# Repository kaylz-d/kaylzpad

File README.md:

# kaylzpad
This is an angel-shaped keypad that I made for Highway to Undercity (Hackpad)!

## Schematic

## PCB

## Model

## BOM
- 5x Cherry MX Switches
- 5x DSA keycaps
- 4x M3x5x4 heatset inserts
- 4x M3x16mm screws
- 3x SK6812 MINI-E LEDs
- 1x XIAO RP2040
- 1x 3D printed case (2 components)

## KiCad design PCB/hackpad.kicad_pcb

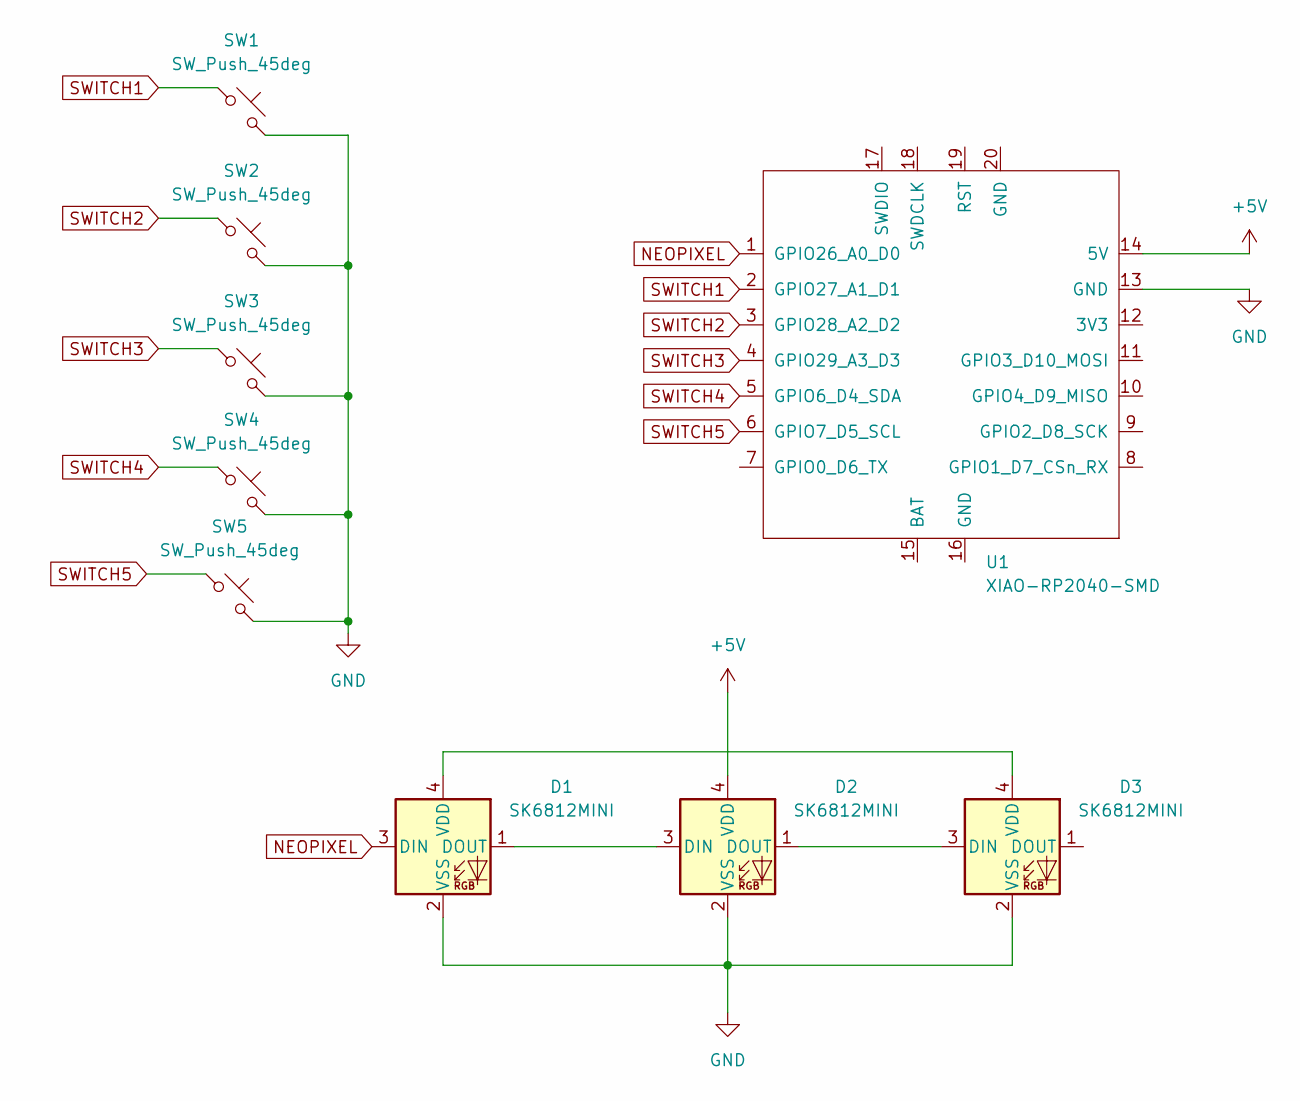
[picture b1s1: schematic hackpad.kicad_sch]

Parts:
D1, D2, D3: SK6812MINI; LED_SK6812MINI_PLCC4_3.5x3.5mm_P1.75mm
SW1, SW2, SW3, SW4, SW5: SW_Push_45deg; SW_Cherry_MX_1.00u_PCB
U1: XIAO-RP2040-SMD; XIAO-RP2040-DIP

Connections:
+5V: D2.4 (VDD), U1.14 (5V)
GND: D1.2 (VSS), D2.2 (VSS), D3.2 (VSS), SW1.2, SW2.2, SW3.2, SW4.2, SW5.2, U1.13 (GND)
NEOPIXEL: D1.3 (DIN), U1.1 (GPIO26_A0_D0)
unnamed: D1.1 (DOUT), D2.3 (DIN)
unnamed: D1.4 (VDD), D3.4 (VDD)
unnamed: D2.1 (DOUT), D3.3 (DIN)
SWITCH1: SW1.1, U1.2 (GPIO27_A1_D1)
SWITCH2: SW2.1, U1.3 (GPIO28_A2_D2)
SWITCH3: SW3.1, U1.4 (GPIO29_A3_D3)
SWITCH4: SW4.1, U1.5 (GPIO6_D4_SDA)
SWITCH5: SW5.1, U1.6 (GPIO7_D5_SCL)

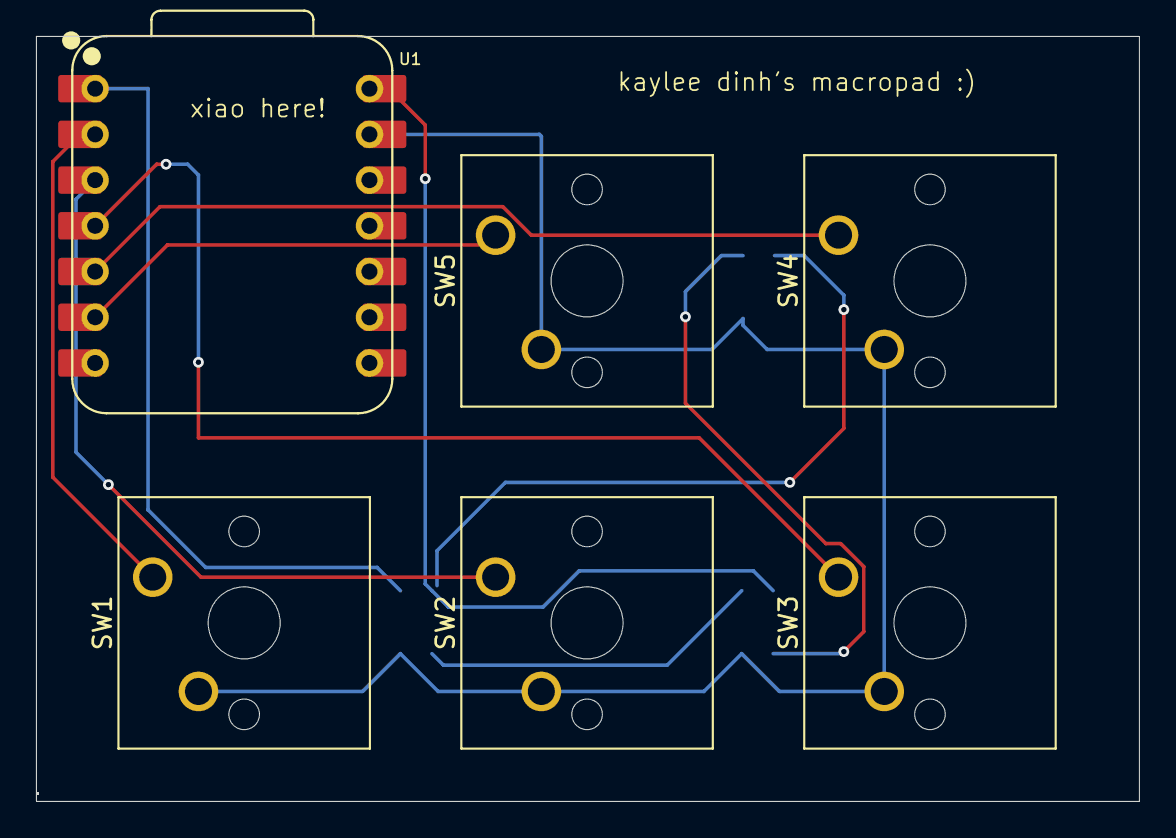
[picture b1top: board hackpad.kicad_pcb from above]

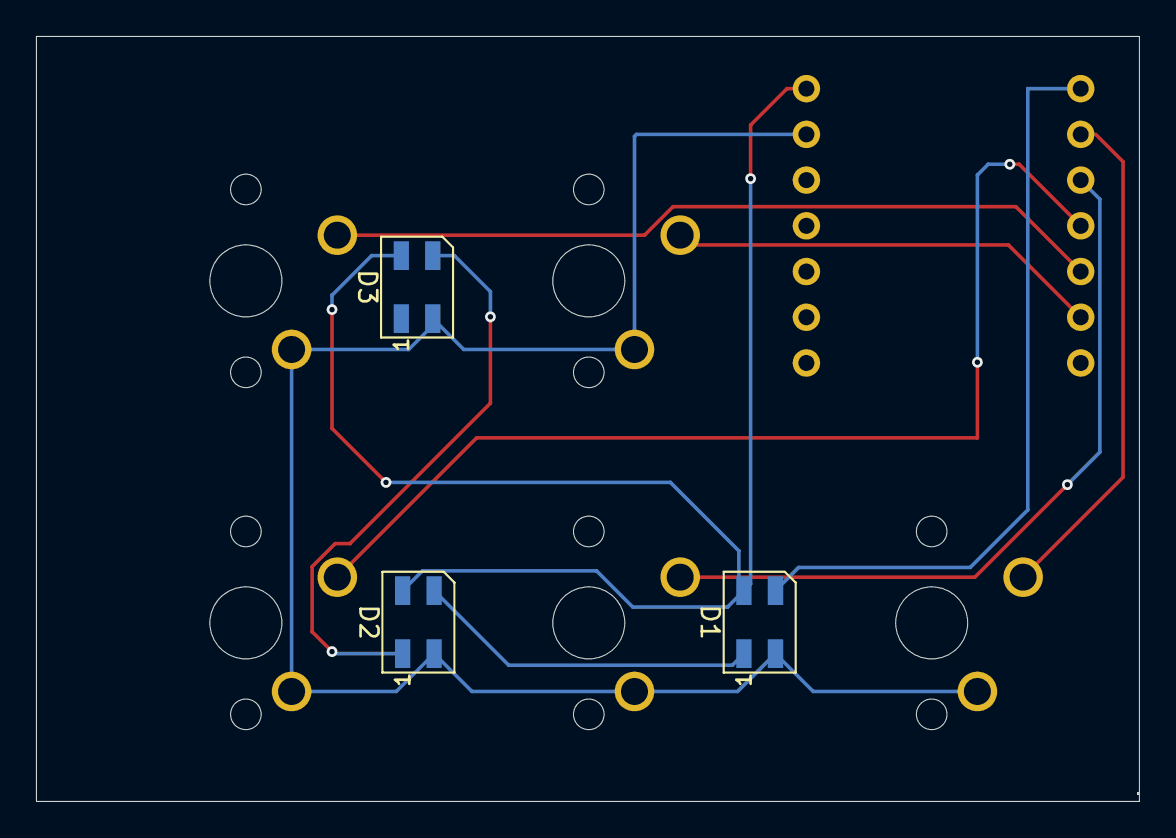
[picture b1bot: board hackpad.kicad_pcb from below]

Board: 2 copper layers, 61.3 x 42.5 mm, 9 parts (3 on the bottom side), 11 nets.

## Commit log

2025-07-09 initial upload
2025-07-09 added images
